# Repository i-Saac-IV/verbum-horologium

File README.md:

# Verbum Horologium
A digital clock that displays time in an analog fashion.

# Table of Contents
- [Features](#features)
- [Fixes and Updates](#fixes-and-updates)
- [Pictures and Video](#pictures-and-video)
- [Hardware and Setup](#hardware-and-setup)
  - [Laser Cut Housing](#laser-cut-housing)
  - [3D Printed Framing](#3d-printed-framing)
  - [Printed Circuit Board](#printed-circuit-board)
  - [Code](#code)
    - [Dependencies](#dependencies)
- [Copyright and Licensing](#copyright-and-licensing)
- [Contact](#contact)

# Features
- Invisible capacitive touch buttons for user input.
- Automatic brightness control via ambient light sensor.
- Night mode, turning off the display when the room is dark.
- Serial passthrough for updating the real-time clock (RTC).

# Fixes and Updates
> [!IMPORTANT]
> This project is currently under development undergoing a major code refactor. Please bear with me while I work on improving functionality.

# Pictures and Video
<table align="center">
  <tr>
    <td align="center">
      <br>
      <b>Demo</b>
    </td>
  </tr>
</table>
<table align="center">
  <tr>
    <td align="center">
      <br>
      <b>Main control board</b>
    </td>
    <td align="center">
      <br>
      <b>Internal wiring</b>
    </td>
    <td align="center">
      <br>
      <b>LED matrix array</b>
    </td>
  </tr>
</table>

# Hardware and Setup

## Laser Cut Housing
All laser cutting files can be found [here](/assets/laser/).

Please insure that:
- The [LED diffuser](/assets/laser/diffusion_white-acrylic.svg) is cut out of white acrylic.
- The [clock face](/assets/laser/clock-face_black-polypropylene.svg) is cut out of a thin and opaque material.
- The [bottom](/assets/laser/bottom-side_black-acrylic.svg) and [sides](/assets/laser/side_black-acrylic.svg) are cut out of an opaque material.

Doing so will ensure the clock performs at its best.

## 3D Printed Framing
The 3D printed components will not be visible from the front of the clock, so do not worry about surface finish or colour. However, several of the prints will have to be paused throughout the print to insert embedded fasteners.

## Printed Circuit Board
The gerber files for PCB manufacturing can be found [here](/assets/pcb/mainboard_v1_14-06-24.zip).

## Code
### Dependencies
This project requires the following external Arduino libraries, please ensure that they are installed:
- [FastLED (v3.10.3)](https://github.com/FastLED/FastLED/tree/3.10.3)
- [RTClib by Adafruit (v2.1.4)](https://github.com/adafruit/RTClib/tree/2.1.4)
- [CAP1188 Library by Adafruit (v1.1.3)](https://github.com/adafruit/Adafruit_CAP1188_Library/tree/1.1.3)

For programming of the Raspberry Pi Pico W via the Arduino IDE I've included the board library I used here:
- [Arduino Pico by Earle F. Philhower, III (v5.6.0)](https://github.com/earlephilhower/arduino-pico/tree/5.6.0)

Open the Arduino IDE, install the code and board libraries mentioned above, plug in your mainboard, and upload the code.

# Copyright and Licensing
See [license](LICENSE) for in depth info.

This project uses the following third-party libraries:

- FastLED (MIT License)
- RTClib (MIT License)
- Adafruit CAP1188 (BSD License)
- Arduino Pico (LGPL License)

Copyright and license terms belong to their respective authors.

Contact me if anything here is incorrect.

# Contact
If you'd like to get in touch, feel free to reach out!
<p>

</p>

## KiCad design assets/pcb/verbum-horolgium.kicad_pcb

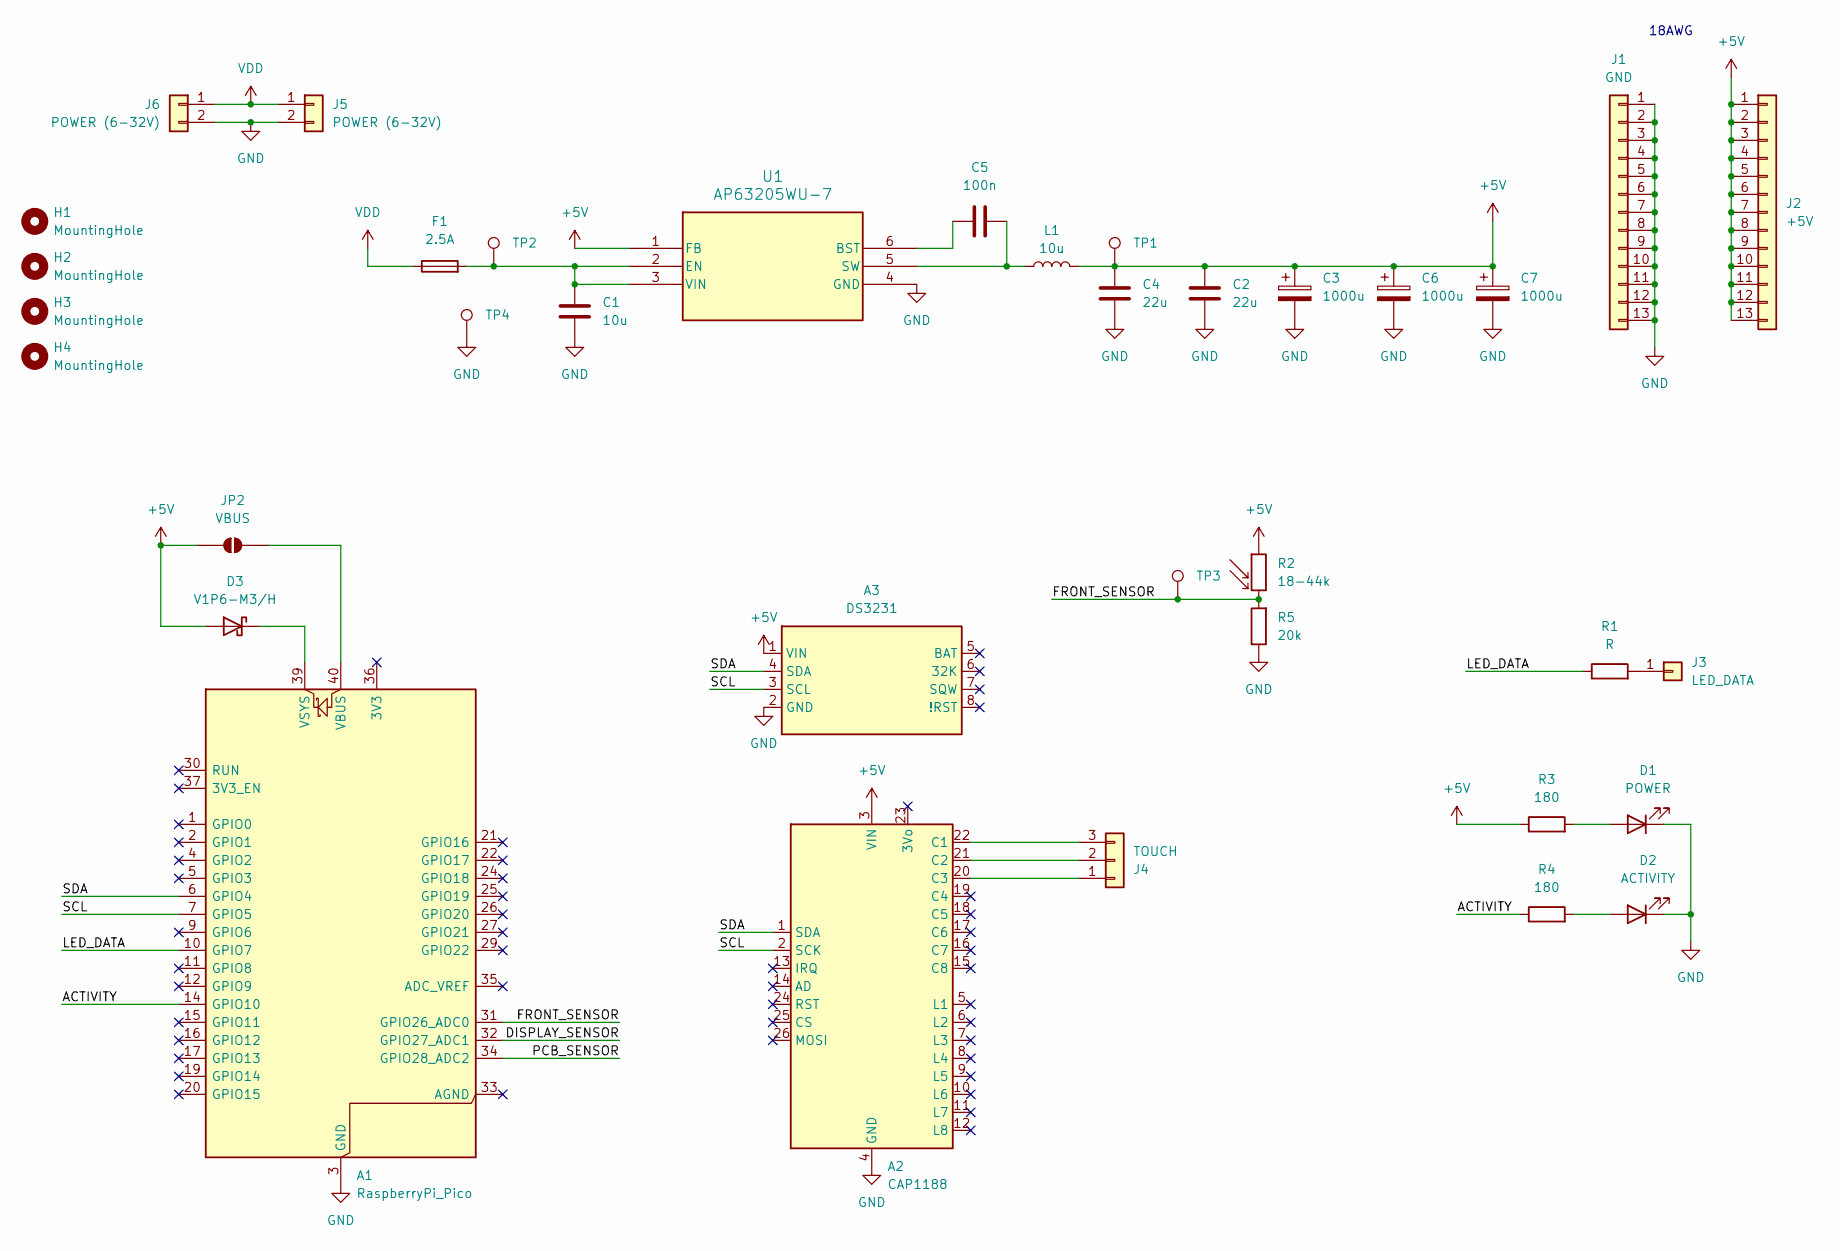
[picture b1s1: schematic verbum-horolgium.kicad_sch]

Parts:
A1: RaspberryPi_Pico; RaspberryPi_Pico_Common_Unspecified
A2: CAP1188; CAP1188-breakout
A3: DS3231; DS3231-breakout
C1: 10u; C_1210_3225Metric
C2, C4: 22u; C_1206_3216Metric
C3, C6, C7: 1000u; CP_Elec_10x10
C5: 100n; C_0805_2012Metric
D1: POWER; LED_1206_3216Metric
D2: ACTIVITY; LED_1206_3216Metric
D3: V1P6-M3/H; D_MicroSMP_LargeCathode
F1: 2.5A; Fuse_0603_1608Metric
H1, H2, H3, H4: MountingHole; MountingHole_3.2mm_M3
J1: GND; SolderWire-1.5sqmm_1x13_P5mm_D1.7mm_OD3mm_Relief
J2: +5V; SolderWire-1.5sqmm_1x13_P5mm_D1.7mm_OD3mm_Relief
J3: LED_DATA; SolderWire-1.5sqmm_1x1_P5mm_D1.7mm_OD3mm_Relief
J4: TOUCH; SolderWire-1.5sqmm_1x3_P5mm_D1.7mm_OD3mm_Relief
J5, J6: POWER (6-32V); SolderWire-1.5sqmm_1x2_P5mm_D1.7mm_OD3mm_Relief
JP2: VBUS; SolderJumper-2_P1.3mm_Open_TrianglePad1.0x1.5mm
L1: 10u; L_Wurth_WE-TPC-1038
R1: R; R_Axial_DIN0207_L6.3mm_D2.5mm_P7.62mm_Horizontal
R2: 18-44k; SolderWire-1.5sqmm_1x2_P5mm_D1.7mm_OD3mm_Relief
R3, R4: 180; R_0603_1608Metric
R5: 20k; R_Axial_DIN0207_L6.3mm_D2.5mm_P7.62mm_Horizontal
TP1, TP2, TP3, TP4: PinHeader_1x01_P1.00mm_Vertical
U1: AP63205WU-7; SOIC_05WU-7_DIO

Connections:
+5V: A2.3 (VIN), A3.1 (VIN), C2.1, C3.1, C4.1, C6.1, C7.1, D3.2 (A), J2.1, J2.2, J2.3, J2.4, J2.5, J2.6, J2.7, J2.8, J2.9, J2.10, J2.11, J2.12, J2.13, JP2.2 (B), L1.2, R2.1, R3.1, TP1.1 (1_1), U1.1 (FB)
/ACTIVITY: A1.14 (GPIO10), R4.1
/DISPLAY_SENSOR: A1.32 (GPIO27_ADC1)
/FRONT_SENSOR: A1.31 (GPIO26_ADC0), R2.2, R5.2, TP3.1 (1_1)
/LED_DATA: A1.10 (GPIO7), R1.1
/PCB_SENSOR: A1.34 (GPIO28_ADC2)
/SCL: A1.7 (GPIO5), A2.2 (SCK), A3.3 (SCL)
/SDA: A1.6 (GPIO4), A2.1 (SDA), A3.4 (SDA)
GND: A1.3 (GND), A1.8 (GND), A1.13 (GND), A1.18 (GND), A1.23 (GND), A1.28 (GND), A1.38 (GND), A2.4 (GND), A3.2 (GND), C1.2, C2.2, C3.2, C4.2, C6.2, C7.2, D1.1 (K), D2.1 (K), J1.1, J1.2, J1.3, J1.4, J1.5, J1.6, J1.7, J1.8, J1.9, J1.10, J1.11, J1.12, J1.13, J5.2, J6.2, R5.1, TP4.1 (1_1), U1.4 (GND)
unnamed: A1.40 (VBUS), JP2.1 (A)
unnamed: A1.39 (VSYS), D3.1 (K)
unnamed: A2.22 (C1), J4.3
unnamed: A2.21 (C2), J4.2
unnamed: A2.20 (C3), J4.1
unnamed: D1.2 (A), R3.2
unnamed: D2.2 (A), R4.2
unnamed: J3.1 (Pin_1_1), R1.2
unnamed: C5.1, U1.6 (BST)
unnamed: C1.1, F1.2, TP2.1 (1_1), U1.2 (EN), U1.3 (VIN)
unnamed: C5.2, L1.1, U1.5 (SW)
VDD: F1.1, J5.1, J6.1

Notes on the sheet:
18AWG

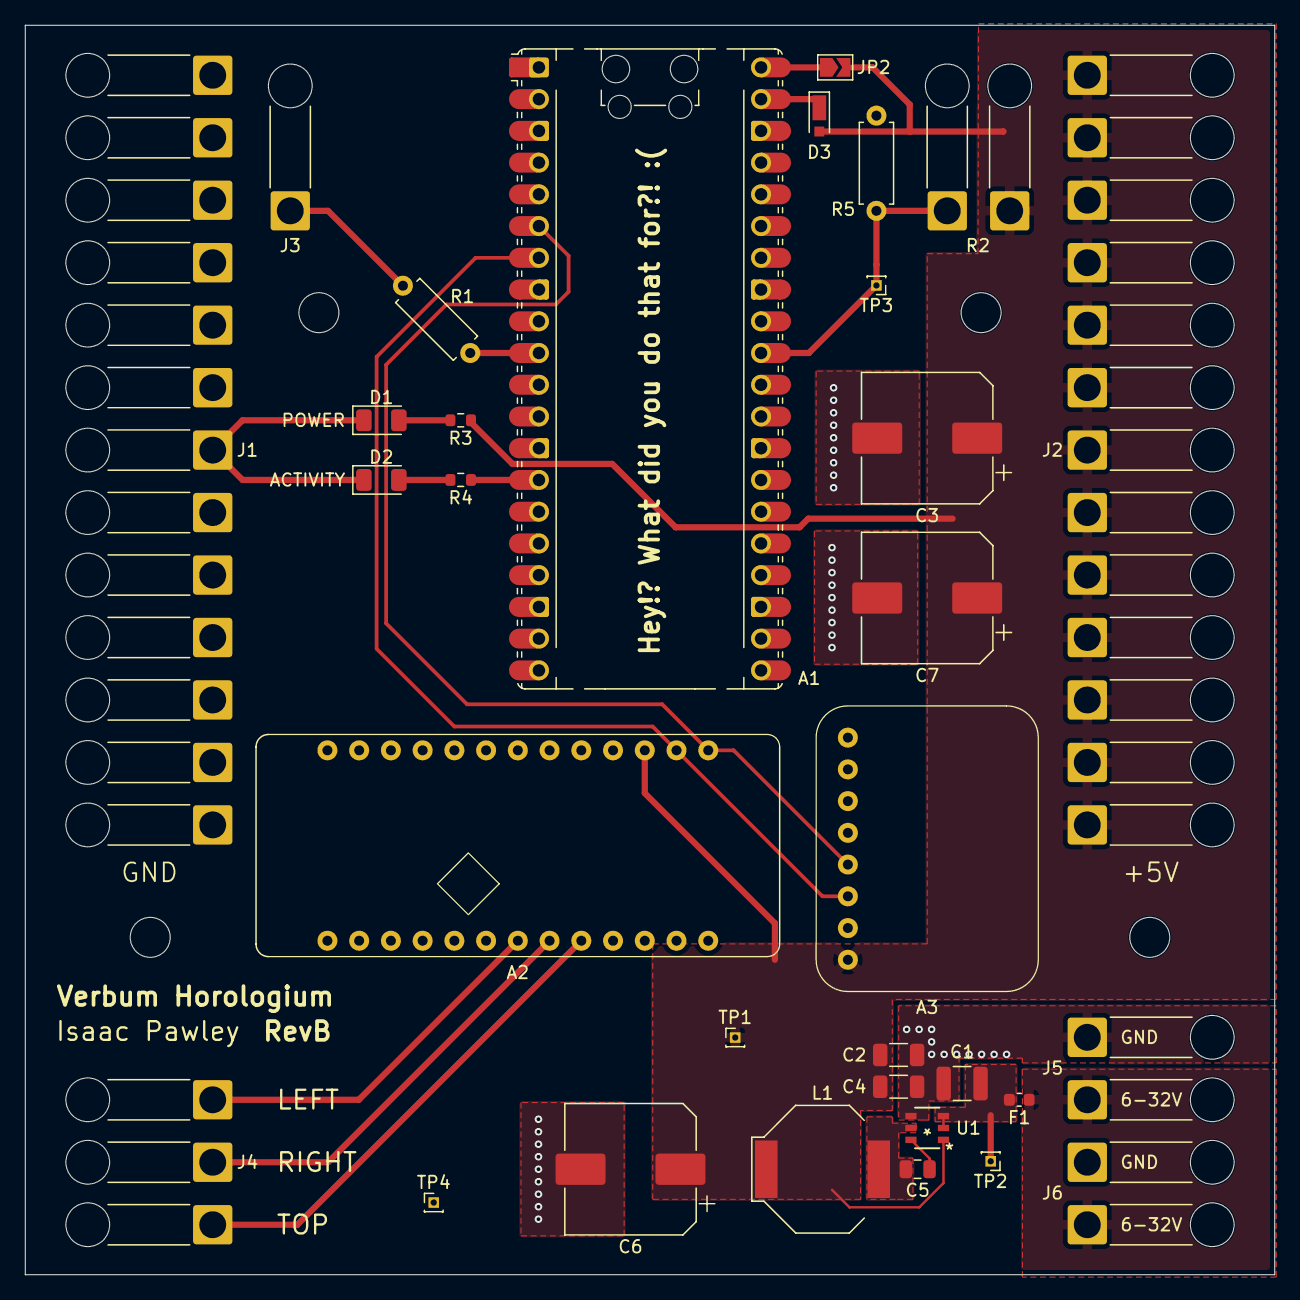
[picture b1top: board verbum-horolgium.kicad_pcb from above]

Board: 2 copper layers, 100.0 x 100.0 mm, 36 parts (1 on the bottom side), 19 nets.

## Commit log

2024-05-09 first commit, added clock face text
2024-05-09 added first version of clockface
2024-06-14 adding all current physical files
2024-06-14 .gitignore update
2024-06-14 reverted .gitignore file
2024-07-14 added sketch, working with reading/setting time
2024-07-15 code updates, now working with matrix and clock
2024-07-15 code workinggit status
2024-07-15 minor bug fixes
2024-08-13 final commit??
2025-11-30 Removed temp file
2026-04-13 docs: added video demo
2026-04-29 chore: updated gitignore for vscode and platformio workflow
2026-04-29 chore: working with platformio
2026-04-29 fix: started code refector
2026-04-29 feat: added bitmap drawing
2026-04-29 feat: word indexing and display working
2026-04-29 feat: added number bitmaps
2026-04-29 fix: mircogl draws number bitmaps
2026-04-29 feat: digital clock working
2026-04-29 fix: reads clock on init
2026-04-29 feat: added extra number bitmaps
2026-04-29 feat: added alternative clock display
2026-05-01 feat: touch buttons working
2026-05-01 chore: added global config file
2026-05-01 fix: modes declaration out of header file
2026-05-01 feat: added support for 12 hour mode
2026-05-03 feat: added scaling for brightness sensors
2026-05-05 fix: matrix dimming works as does config
2026-05-14 docs: updated to include photos
2026-05-15 docs: added video to readme
2026-05-15 fix: saved readme
2026-05-15 fix: changed video size
2026-05-15 docs: removed extra pictures
2026-05-15 docs: fixed grammer and added external links
2026-05-15 docs: removed external licenses
2026-05-15 docs: fixed table of contents
2026-05-15 docs: fixed grammar
2026-05-17 feat: added basic work clock
2026-05-18 fix: added word clock into main code
2026-05-19 feat: started fsm development, input events working
2026-05-19 fix: minor fix to spelling
2026-05-19 feat: basic fsm functionality working
2026-05-20 fix: all tasks running via task scheduler
2026-05-20 chore: updated code to mach style
2026-05-20 chore: clockface changes on long presses of side buttons
2026-05-20 feat: added very basic reaction to user input
2026-05-20 fix: increased task frequencies
2026-05-20 chore: removed old code
2026-05-21 chore: minor change to how messages are printed
2026-05-21 chore: updated ordering and types of data
2026-05-21 feat: added basic settings screens
2026-05-21 feat: added settings adjustment feature
2026-05-21 feat: added progress bar clock
2026-05-21 fix: display brightness now set to lrd readings on display init
2026-05-21 fix: added and using macros for display width and height
2026-05-21 chore: refactored repeating code, still not great however
2026-05-21 feat: added the words day and night to the map
2026-05-21 chore: ignoring .clangd file
2026-06-18 feat: added changing colour palette mode
2026-06-18 fix: updated app datatype name
2026-06-18 fix: update app datatype name
2026-06-19 fix: added external access to led_matrix
2026-06-19 chore: added rendering layers
2026-06-19 chore: updated microgl to use layers and masks
2026-06-19 chore: added blending for layers
2026-06-19 fix: removed email
2026-06-19 fix: indicator is now displayed
2026-06-19 fix: removed colour macros
2026-06-19 feat: added screen change animations
2026-06-19 feat: added screen transitions
2026-06-19 chore: added transition config option
2026-06-19 chore: refinded transitions
2026-06-19 fix: clock display functions no longer call rtc_gettime
2026-06-19 fix: fixed arguments
2026-06-19 feat: renders transitions on time changes
2026-06-20 fix: removed config
2026-06-20 fix: changed time return type
2026-06-20 feat: renderer now shows seconds heartbeat
2026-06-20 fix: rendering settings menu again
2026-06-20 refactor: exposed display mapping function to remove duplicate code
2026-06-20 fix: removed render target width and height as it was confusing
2026-06-20 fix: renamed folder
2026-06-20 fix: progress clock now displays the correct time after midday
2026-06-20 feat: clock colours are picked from palette
2026-06-20 fix: setup colour palette
2026-06-20 feat: added colour palettes
2026-06-20 chore: animating colour changes - wip
2026-06-21 chore: saving and prepairing for revert
2026-06-21 chore: revert last 5 commits
2026-06-21 chore: updated gitignore for new pcb files
2026-06-21 chore: deleted old pcb files
2026-06-21 chore: added new pcb files
2026-06-21 chore: added palette datatypes
2026-06-22 chore: fsm updateded to change palettes
2026-06-22 fix: clocks are now passed colour palette
2026-06-22 feat: render now animates colour palette transitions
2026-06-22 feat: all clocks now use colours from given palette
2026-06-22 fix: color mode settings function call
2026-06-22 feat: auto sleep function working
2026-06-22 fix: removed touch reaction
2026-06-22 feat: randomising colour palettes working
2026-06-22 fix: reduced the size of the colour palettes to improve contrast
2026-06-22 fix: random colour palette given better limits
2026-06-22 fix: random colours are always 90 degress apart and limited in lowest saturation
2026-06-22 feat: added cycling demo mode
2026-06-22 fix: updated timings for demo retriggers
2026-06-22 feat: added an extra rainbow setting
2026-06-22 fix: clear layers and compose now belong to the gl
2026-06-22 chore: removed clear and compose functions
2026-06-22 fix: exposed layout for startup
2026-06-22 feat: created startup animation
2026-06-23 fix: heartbeat moves between screen better and updates during transitions
2026-06-23 fix: heartbeat now beats regulary
2026-06-23 chore: removed unused code
2026-06-23 feat: added setting of the time to fsm
2026-06-23 feat: added time setting screens
2026-06-23 feat: added version printing
2026-06-24 chore: added footprints and symbols
2026-06-24 chore: basic schematic complete
2026-06-29 chore: pcb layout complete
2026-06-29 chore: added text to front silkscreen
2026-06-29 fix: added mounting holes
2026-06-29 chore: exported rev b gerber files
